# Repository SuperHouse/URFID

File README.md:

Priority 1 Designs uRFID Module Breakout
=========================================
Copyright 2013 SuperHouse Pty Ltd www.superhouse.tv  

Breaks out a uRFID module from Priority 1 Designs. Ideal for making
your own RFID door lock with implantable RFID tags.

Features:

 * External status LEDs
 * Easy connection header

More information is available at:

  http://www.superhouse.tv/urfid

INSTALLATION
------------
The design is saved as an EAGLE project. EAGLE PCB design software is
available from www.cadsoftusa.com free for non-commercial use. To use
this project download it and place the directory containing these files
into the "eagle" directory on your computer. Then open EAGLE and
navigate to the project.

DISTRIBUTION
------------
The specific terms of distribution of this project are governed by the
license referenced below.

LICENSE
-------
Licensed under the TAPR Open Hardware License (www.tapr.org/OHL).
The "license" folder within this repository also contains a copy of
this license in plain text format.

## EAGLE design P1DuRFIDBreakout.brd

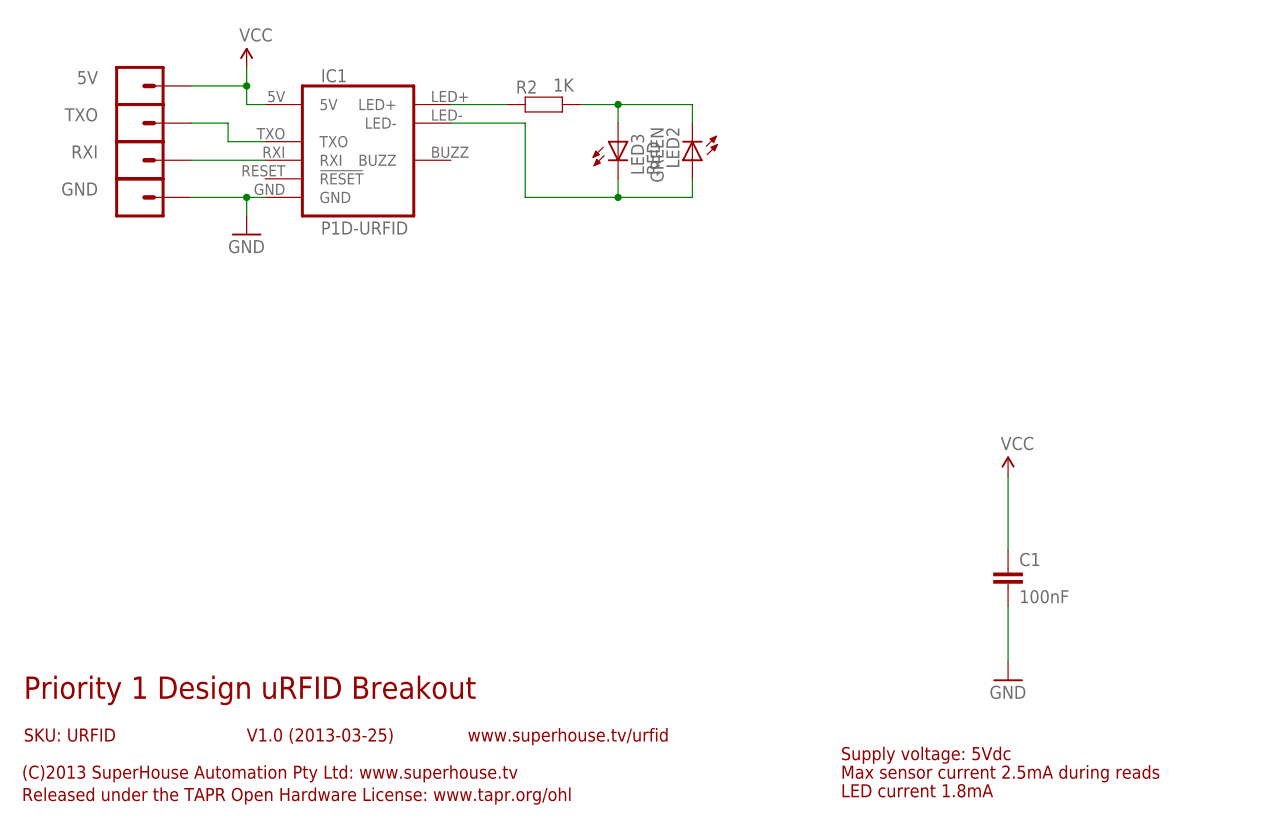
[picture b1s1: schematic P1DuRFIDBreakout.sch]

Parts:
5V: M01PTH; 1X01
C1: 100nF; 0603
GND: M01PTH; 1X01
IC1: P1D-URFID; URFID
LED2: GREEN; LED3MM
LED3: RED; LED3MM
R2: 1K; 0603
RXI: M01PTH; 1X01
TXO: M01PTH; 1X01

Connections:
GND: C1.2, GND.1, IC1.GND
unnamed: IC1.LED+, R2.2
unnamed: LED2.K (C), LED3.A, R2.1
unnamed: IC1.LED-, LED2.A, LED3.K (C)
unnamed: IC1.RXI, RXI.1
unnamed: IC1.TXO, TXO.1
VCC: 5V.1, C1.1, IC1.5V

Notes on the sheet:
Priority 1 Design uRFID Breakout
V1.0 (2013-03-25)
SKU: URFID
(C)2013 SuperHouse Automation Pty Ltd: www.superhouse.tv
Released under the TAPR Open Hardware License: www.tapr.org/ohl
www.superhouse.tv/urfid
Supply voltage: 5Vdc
Max sensor current 2.5mA during reads
LED current 1.8mA

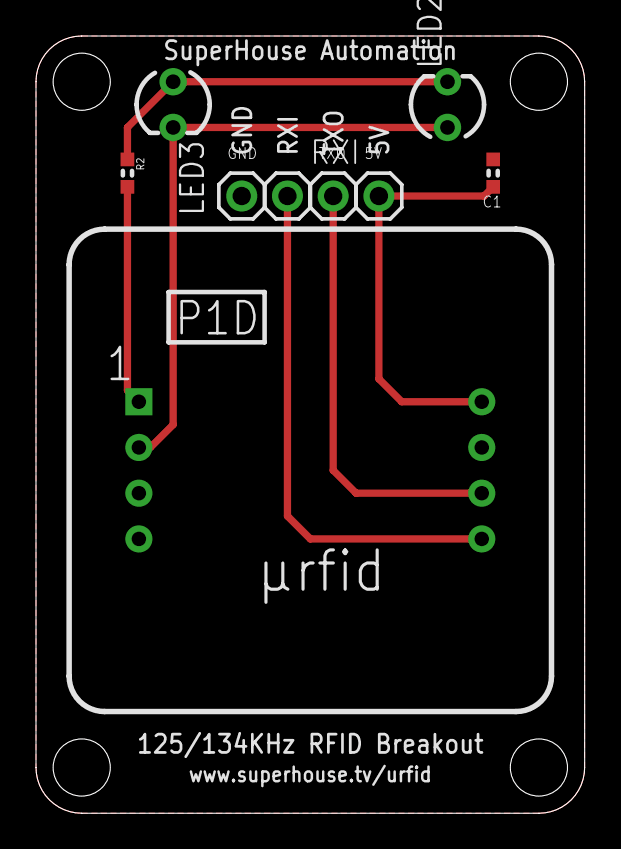
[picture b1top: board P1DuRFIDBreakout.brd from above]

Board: 2 copper layers, 30.5 x 43.2 mm, 9 parts (0 on the bottom side), 7 nets.

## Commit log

2018-03-28 Imported old project
2018-03-28 Renamed project files

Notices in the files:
P1DuRFIDBreakout.brd:
(C)2012 SuperHouse Automation
